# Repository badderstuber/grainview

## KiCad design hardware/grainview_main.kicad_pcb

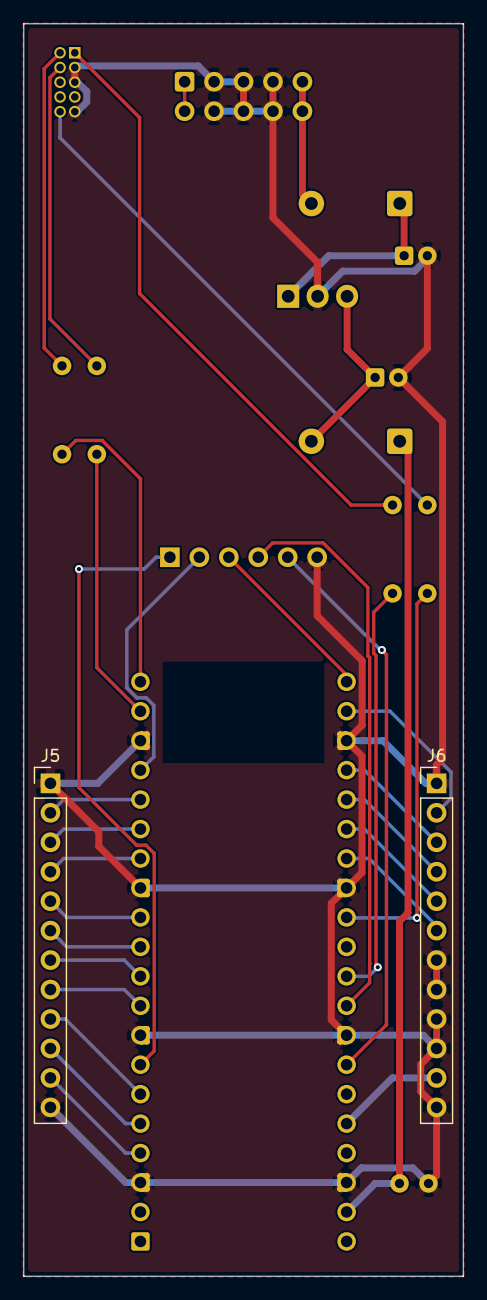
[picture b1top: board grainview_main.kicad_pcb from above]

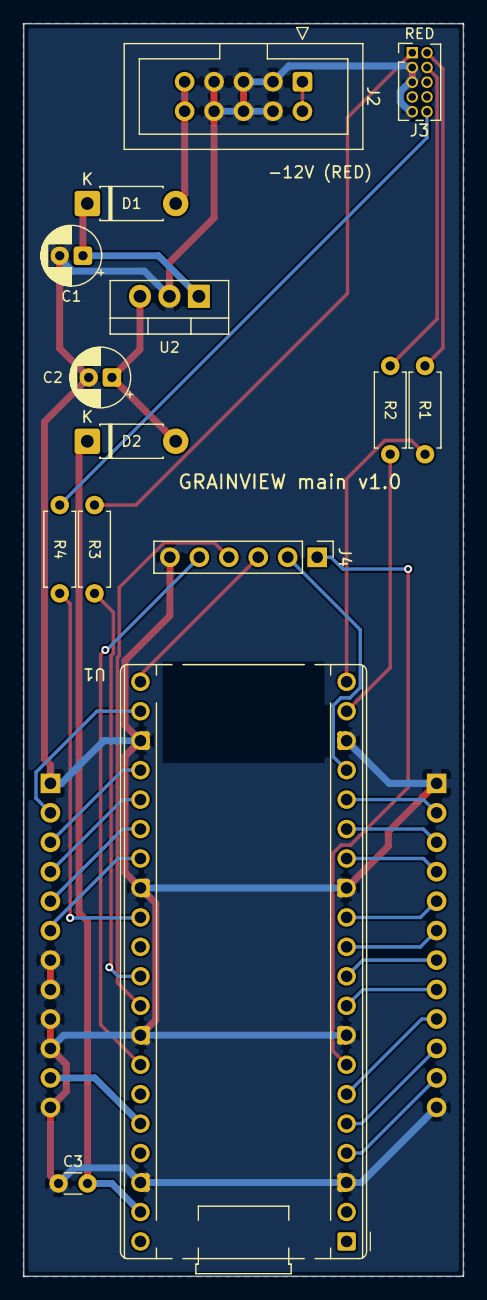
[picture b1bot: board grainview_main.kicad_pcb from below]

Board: 2 copper layers, 37.9 x 108.0 mm, 16 parts (14 on the bottom side), 35 nets.

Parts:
C1: 10uF 25V; CP_Radial_D5.0mm_P2.00mm
C2: 10uF 16V; CP_Radial_D5.0mm_P2.00mm
C3: 100nF; C_Disc_D3.0mm_W1.6mm_P2.50mm
D1: 1N5817 reverse prot.; D_DO-41_SOD81_P7.62mm_Horizontal
D2: 1N5817 5V->VSYS; D_DO-41_SOD81_P7.62mm_Horizontal
J2: Eurorack power; IDC-Header_2x05_P2.54mm_Vertical
J3: SWD to JTRACE; PinHeader_2x05_P1.27mm_Vertical
J4: spare GPIO; PinHeader_1x06_P2.54mm_Vertical
J5, J6: 1x12 male (board link); PinHeader_1x12_P2.54mm_Vertical
R1, R2: 47R; R_Axial_DIN0207_L6.3mm_D2.5mm_P7.62mm_Horizontal
R3: 1k; R_Axial_DIN0207_L6.3mm_D2.5mm_P7.62mm_Horizontal
R4: 1k DNP; R_Axial_DIN0207_L6.3mm_D2.5mm_P7.62mm_Horizontal
U1: Pico 2 W (sockets); RaspberryPi_Pico_Common_THT
U2: R-78E5.0 / TSR1-2450 / 7805; TO-220-3_Vertical

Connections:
3V3: J6.11, U1.36
AB: J5.3, U1.15
BACK: J5.8, U1.9
CS: J6.2, U1.22
DC: J6.5, U1.26
ENC_A: J5.11, U1.4
ENC_B: J5.10, U1.5
ENC_SW: J5.9, U1.6
FILE: J5.6, U1.11
GND: C1.2, C2.2, C3.2, J2.3, J2.4, J2.5, J2.6, J2.7, J2.8, J3.3, J3.5, J3.9, J4.6, J5.1, J5.12, J6.1, J6.7, J6.8, J6.9, J6.10, J6.12, U1.3, U1.8, U1.13, U1.18, U1.23, U1.28, U1.33, U1.38, U2.2
GP5: J4.1, U1.7
GP13: J4.2, U1.17
GP16: J4.3, U1.21
GP27: J4.4, U1.32
GP28: J4.5, U1.34
M12V: J2.1, J2.2
MOSI: J6.4, U1.25
NRST: J3.10, R4.1
NRST_P: R4.2, U1.29
P5V: C2.1, D2.2, U2.3
P12V: C1.1, D1.1, U2.1
P12V_IN: D1.2, J2.9, J2.10
RST: J6.6, U1.27
SCK: J6.3, U1.24
SETUP: J5.2, U1.16
SOUND_L: J5.5, U1.12
SOUND_R: J5.4, U1.14
SWCLK: J3.4, R2.1
SWCLK_P: R2.2, U1.19
SWDIO: J3.2, R1.1
SWDIO_P: R1.2, U1.20
VIEW: J5.7, U1.10
VSYS: C3.1, D2.1, U1.39
VTREF: J3.1, R3.1
VTREF_P: R3.2, U1.31

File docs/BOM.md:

# GRAINVIEW v1.0 — parts list (one module)

Boards: JLC order 2026-10-14 (panel, control, main). Spec: HARDWARE.md.
"Have?" = what Leo already owns (as of 2026-10-14).

## Control board (front)
| Ref | Qty | Part | Notes | Have? |
|---|---|---|---|---|
| SW1–SW7 | 7 | APEM **PHAP5-30VA2K2T2N2** tact switch (7.3 mm, 160 g, THT) | Switch Electronics UK | buy (+ spares) |
| — | 7 | APEM **U5532** black 4.5 mm round cap | Switch Electronics, sold in 10s | buy |
| ENC1 | 1 | EC11 push encoder, vertical, 20 mm shaft, **7 mm body** (feet → start of thread) | the breadboard one fits; a spare must be ≥ 6.3 mm body | have 1 |
| — | 1 | knob for the encoder shaft | e.g. Thonk; match the shaft (D or knurled) | buy |
| J1 | 1 | Adafruit 4741 1.5" OLED, its own header soldered in | **cut the bottom-right tab first** | have |
| J5, J6 | 2 | 1x12 female header, 2.54 mm, 8.5 mm tall | or cut from 1x20 / 1x40 strips (lose one position per cut) | buy |
| — | 1–2 | 3 mm double-sided foam pad | under the OLED's bottom corners | buy/have |
| — | (opt.) | M2.5 nylon screw + nut + washers to ~2.5 mm | bottom-left OLED hole, if you want it screwed down | optional |

## Main board (back)
| Ref | Qty | Part | Notes | Have? |
|---|---|---|---|---|
| U1 | 1 | Raspberry Pi **Pico 2 WH** | | have |
| — | 2 | 1x20 female header, 2.54 mm, 8.5 mm | Pico sockets | buy |
| J5, J6 | 2 | 1x12 male header, 2.54 mm | break off a 1x40 strip | buy/have |
| J4 | 1 | 1x6 male header, 2.54 mm | same strip; optional (spare GPIOs) | buy/have |
| J2 | 1 | 2x5 shrouded box header, 2.54 mm (Eurorack power) | | buy |
| — | 1 | Eurorack power ribbon, 10-to-16 pin | to the bus board | have? |
| J3 | 1 | 2x5 **1.27 mm** male pin header, THT (SWD) | same part as the one soldered into JTRACE | buy |
| — | 1 | 10-pin 1.27 mm SWD ribbon (female both ends) | the Olimex grey cable works; a 2nd keeps the ST-Link setup intact | have 1 |
| U2 | 1 | **ST L7805CV** 5 V regulator, TO-220 (Switch Electronics, with the buttons) | v1 choice. Stands ~20 mm, so the module is ~41 mm deep: check the case. Runs warm (0.5–1 W, fine). Drop-in upgrade later: RECOM **R-78E5.0-0.5** / Traco **TSR 1-2450** (~10 mm, cool) | buy |
| D1, D2 | 2 | **1N5817** Schottky diode | | buy/have |
| C1 | 1 | 10 µF electrolytic, ≥ 25 V, 5 mm dia, 2 mm pitch | 35 V is fine | have? |
| C2 | 1 | 10 µF electrolytic, ≥ 16 V, 5 mm dia, 2 mm pitch | | have? |
| C3 | 1 | 100 nF ceramic, 2.5 mm pitch | | have? |
| R1, R2 | 2 | 47 Ω, ¼ W axial | SWD series resistors | have? |
| R3 | 1 | 1 kΩ, ¼ W axial | VTREF sense | have? |
| R4 | 0 | 1 kΩ | **do not fit** (nRESET, unused) | — |

## Panel
| Qty | Part | Notes |
|---|---|---|
| 2 | M3 rack screws (+ nylon washers) | usually come with the case |

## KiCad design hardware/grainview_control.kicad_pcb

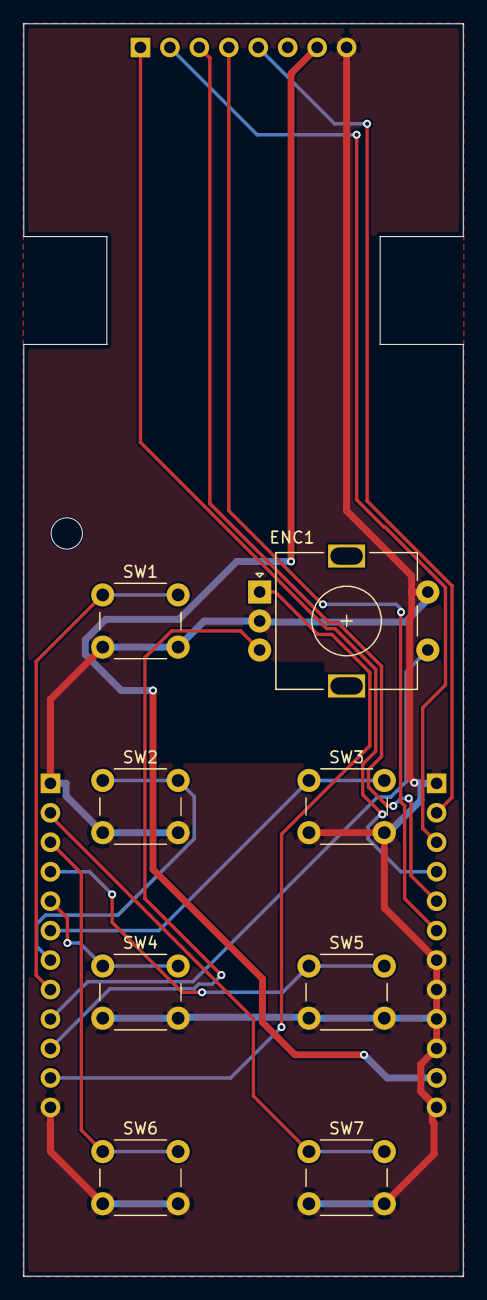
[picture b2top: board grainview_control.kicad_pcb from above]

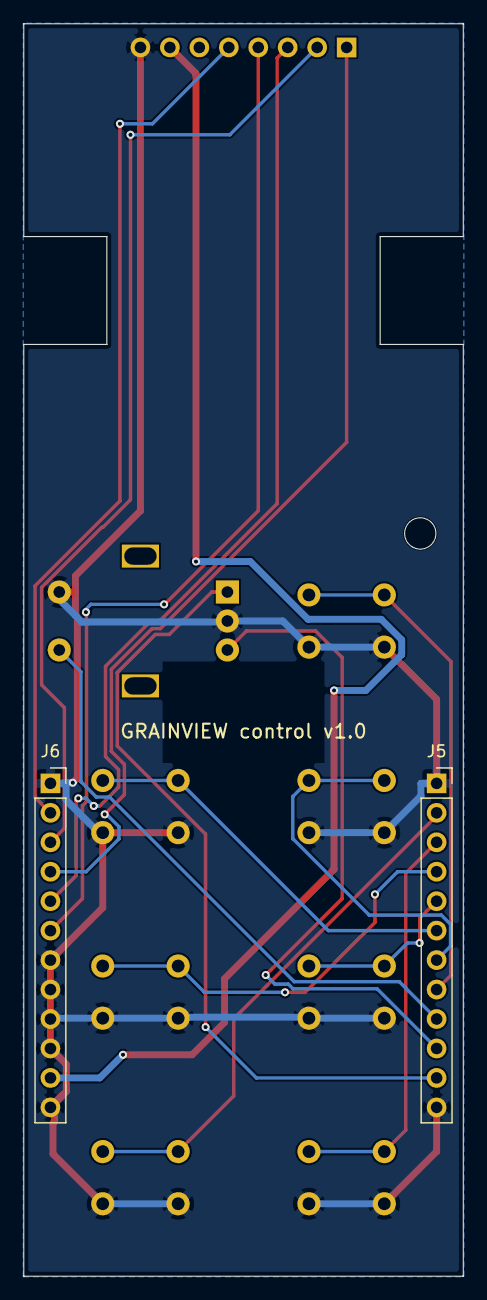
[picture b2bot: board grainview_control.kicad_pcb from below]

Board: 2 copper layers, 37.9 x 108.0 mm, 11 parts (2 on the bottom side), 17 nets.

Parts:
ENC1: EC11 push encoder (7 mm body); RotaryEncoder_Alps_EC11E-Switch_Vertical_H20mm
J1: Adafruit 4741 OLED (own header); Adafruit_4741_OLED
J5, J6: 1x12 female 8.5 mm (board link); PinSocket_1x12_P2.54mm_Vertical
SW1: BACK PHAP5-30VA2K + U5532; SW_PUSH_6mm
SW2: VIEW PHAP5-30VA2K + U5532; SW_PUSH_6mm
SW3: FILE PHAP5-30VA2K + U5532; SW_PUSH_6mm
SW4: SOUND‹ PHAP5-30VA2K + U5532; SW_PUSH_6mm
SW5: SOUND› PHAP5-30VA2K + U5532; SW_PUSH_6mm
SW6: A/B PHAP5-30VA2K + U5532; SW_PUSH_6mm
SW7: SETUP PHAP5-30VA2K + U5532; SW_PUSH_6mm

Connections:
3V3: J1.7, J6.11
AB: J5.3, SW6.1
BACK: J5.8, SW1.1
CS: J1.5, J6.2
DC: J1.3, J6.5
ENC_A: ENC1.A, J5.11
ENC_B: ENC1.B, J5.10
ENC_SW: ENC1.S1, J5.9
FILE: J5.6, SW3.1
GND: ENC1.C, ENC1.S2, J1.8, J5.1, J5.12, J6.1, J6.7, J6.8, J6.9, J6.10, J6.12, SW1.2, SW2.2, SW3.2, SW4.2, SW5.2, SW6.2, SW7.2
MOSI: J1.1, J6.4
RST: J1.4, J6.6
SCK: J1.2, J6.3
SETUP: J5.2, SW7.1
SOUND_L: J5.5, SW4.1
SOUND_R: J5.4, SW5.1
VIEW: J5.7, SW2.1

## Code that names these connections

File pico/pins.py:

# GRAINVIEW breadboard pin map (Pico 2 WH). Source of truth: docs/PINMAP.md.
# All inputs are active-low with internal PULL-UPs (never pull-downs: RP2350 erratum E9).

# Screen: SSD1327 on SPI0
SPI_ID = 0
SCR_SCK = 18   # Clk
SCR_MOSI = 19  # Data
SCR_CS = 17
SCR_DC = 20
SCR_RST = 21

# Encoder (bare EC11, common to GND)
# Wired A->GP2, B->GP3, but this encoder counts CW as negative that way, so swapped here.
ENC_A = 3
ENC_B = 2
ENC_SW = 4

# Buttons, panel order top -> bottom
BUTTONS = (
    ("BACK", 6),
    ("VIEW", 7),
    ("FILE", 8),
    ("SOUND<", 9),
    ("SOUND>", 10),
    ("A/B", 11),
    ("SETUP", 12),
)

# SWD to the Multigrain (J3 -> JTRACE)
SWCLK = 14
SWDIO = 15
VTREF = 26     # ADC0: the Multigrain's 3.3 V (through 1 kOhm) = it's powered

# Reserved: debug UART 0/1

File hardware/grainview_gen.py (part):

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

def placer(b, n):
    def part(lib, name, ref, pins, a, b_, d, at, value="", back=True):
        f = footprint(b, lib, name, ref, 0, 0, back=back, value=value)
        orient(f, a, b_, d)
        place_at_pad(f, a, *at)
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        sw.SetPosition(sw.GetPosition() + V(x, y) - c)
        n.connect(sw, {"1": net, "2": "GND"})

    link(placer(b, n), "PinSocket", back=True)
    text(b, "GRAINVIEW control v1.0", CX, 71.5, h=1.2, layer=pcbnew.B_SilkS)
    return b

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# ---------------------------------------------------------------- main PCB ------
def main_pcb():
    """Rear board: link headers on the front (facing the control board); Pico in sockets,
    power entry, SWD and spare-GPIO headers on the back."""
    b = pcbnew.CreateEmptyBoard()
    b.SetCopperLayerCount(2)
    n = Nets(b)
    outline(b, [(PCB_X0, PCB_Y0), (PCB_X1, PCB_Y0), (PCB_X1, PCB_Y1), (PCB_X0, PCB_Y1)])
    antenna_keepout(b)
    part = placer(b, n)
    link(part, "PinHeader", back=False)

    # Pico 2 W(H) (back) in 2x 1x20 sockets
    p = footprint(b, "Module", "RaspberryPi_Pico_Common_THT", "U1", 0, 0, back=True,
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    R = ("Resistor_THT", "R_Axial_DIN0207_L6.3mm_D2.5mm_P7.62mm_Horizontal")
    D = ("Diode_THT", "D_DO-41_SOD81_P7.62mm_Horizontal")

    # everything else on the back, above the Pico, placed for short runs to the Pico pins
    # (the antenna keep-out blocks the middle above the Pico, so runs go down the two side
    # channels between the Pico's rows and the link strips):
    #   power chain down the right side (VSYS is the Pico's pin 39, bottom right),
    #   SWD header top left with R1/R2 on the left (GP14/15 = pins 19/20, top left) and R3/R4
    #   on the right (GP26/22 = pins 31/29, right row), spare-GPIO header just above the Pico.
    part("Connector_IDC", "IDC-Header_2x05_P2.54mm_Vertical", "J2",
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    part("Connector_PinHeader_1.27mm", "PinHeader_2x05_P1.27mm_Vertical", "J3",
         {"1": "VTREF", "2": "SWDIO", "3": "GND", "4": "SWCLK", "5": "GND", "9": "GND",
          "10": "NRST"}, "1", "9", "+y", (5.6, 13.0), value="SWD to JTRACE")
    text(b, "RED", 4.97, 11.35, h=0.9, layer=pcbnew.B_SilkS)   # ribbon stripe = pin 1 (VTREF)
    part("Connector_PinHeader_2.54mm", "PinHeader_1x06_P2.54mm_Vertical", "J4",
         {"1": "GP5", "2": "GP13", "3": "GP16", "4": "GP27", "5": "GP28", "6": "GND"},
         "1", "6", "+x", (13.8, 56.5), value="spare GPIO")
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    part(*D, "D2", {"1": "VSYS", "2": "P5V"}, "2", "1", "+x", (26.0, 46.5),
         value="1N5817 5V->VSYS")
    part("Capacitor_THT", "C_Disc_D3.0mm_W1.6mm_P2.50mm", "C3", {"1": "VSYS", "2": "GND"},
         "1", "2", "+x", (33.6, 110.5), value="100nF")       # at the Pico's VSYS pin
    for i, (a, c, v, x) in enumerate([("SWDIO_P", "SWDIO", "47R", 4.5),
                                      ("SWCLK_P", "SWCLK", "47R", 7.5),
                                      ("VTREF_P", "VTREF", "1k", 33.0),
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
